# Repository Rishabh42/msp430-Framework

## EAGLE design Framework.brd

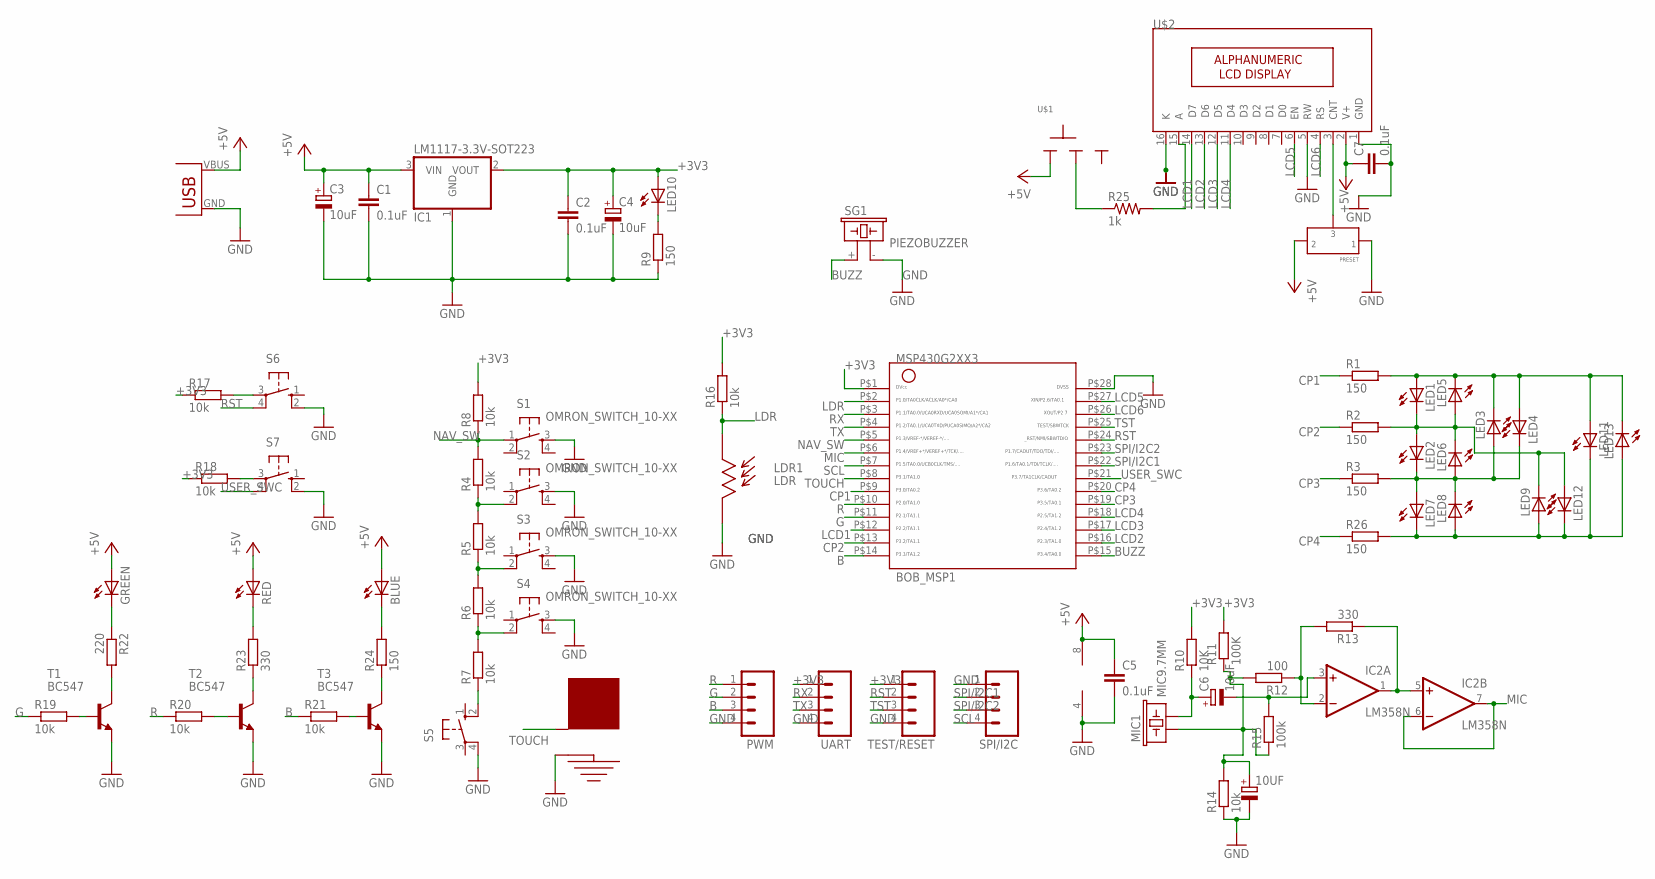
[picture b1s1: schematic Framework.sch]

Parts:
10UF: CAPACITOR-ELECTROLYTICE2.5-6; E2,5-6
BLUE: LED-BLU-5MM; LED-5MM
BOB_MSP1: BOB_MSP_28PIN
C1, C2, C5, C7: 0.1uF; C025-025X050
C3, C4, C6: 10uF; E2,5-6
GREEN: LED-RED-5MM; LED-5MM
IC1: LM1117-3.3V-SOT223; SOT223
IC2: LM358N; DIL08
LDR1: LDR; LDR-5MM
LED1, LED2, LED3, LED4, LED5, LED6, LED7, LED8, LED9, LED10, LED11, LED12, LED13: LED-RED-3MM; LED-3MM
MIC1: MIC9.7MM; MIC-9.7MM
PWM: M04; 04P
R1, R2, R3, R9, R24, R26: 150; 0204/7
R4, R5, R6, R7, R8, R14, R16, R17, R18, R19, R20, R21: 10k; 0204/7
R10: 10K; 0204/7
R11: 100K; 0204/7
R12: 100; 0204/7
R13, R23: 330; 0204/7
R15: 100k; 0204/7
R22: 220; 0204/7
R25: 1k; 0207/10
RED: LED-GRN-5MM; LED-5MM
S1, S2, S3, S4: OMRON_SWITCH_10-XX; B3F-10XX
S5: PUSH-BUTTON-6MM; B3F-10XX
S6, S7: 10-XX; B3F-10XX
SG1: PIEZOBUZZER
SPI/I2C: M04; 04P
T1, T2, T3: BC547; TO92
TEST/RESET: M04; 04P
TOUCH1: TOUCHPAD-20MM
U$1: SLIDE-SWITCH-BIG; SLIDE-SPDT-2.5X5-WITH-SUPPORT
U$2: CHAR-LCD-16X2; 16X2-LCD-WITH-MOUNT
U$3: USB-POWER; MINI-USB-POWER
U$4: PRESET; PRESET-LR
UART: M04; 04P

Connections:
+3V3: BOB_MSP1.P$1 (1), C2.1, C4.+, IC1.2 (VOUT), LED10.A, R8.2, R10.2, R11.2, R16.2, R17.1, R18.1, TEST/RESET.1, UART.1
B: BOB_MSP1.P$14 (14), PWM.3, R21.1
BLUE: BLUE.K (C), R24.2
BUZZ: BOB_MSP1.P$15 (15), SG1.+ (1)
CP1: BOB_MSP1.P$9 (9), R1.1
CP2: BOB_MSP1.P$13 (13), R2.1
CP3: BOB_MSP1.P$19 (19), R3.1
CP4: BOB_MSP1.P$20 (20), R26.1
G: BOB_MSP1.P$11 (11), PWM.2, R19.1
GND: 10UF.-, BOB_MSP1.P$28 (28), C1.2, C2.2, C3.-, C4.-, C5.2, C7.2, IC1.1 (GND), IC2.4 (V-), LDR1.P$2, PWM.4, R9.1, R14.1, S1.3 (S), S2.3 (S), S3.3 (S), S4.3 (S), S5.4 (P1), S6.2 (S1), S7.2 (S1), SG1.- (2), SPI/I2C.1, T1.1 (E), T2.1 (E), T3.1 (E), TEST/RESET.4, TOUCH1.GND, U$2.1 (GND), U$2.5 (RW), U$2.16 (K), U$3.GND, U$4.P$1 (1), UART.4
LCD1: BOB_MSP1.P$12 (12), U$2.14 (D7)
LCD2: BOB_MSP1.P$16 (16), U$2.13 (D6)
LCD3: BOB_MSP1.P$17 (17), U$2.12 (D5)
LCD4: BOB_MSP1.P$18 (18), U$2.11 (D4)
LCD5: BOB_MSP1.P$27 (27), U$2.6 (EN)
LCD6: BOB_MSP1.P$26 (26), U$2.4 (RS)
LDR: BOB_MSP1.P$2 (2), LDR1.P$1, R16.1
MIC: BOB_MSP1.P$6 (6), IC2.6 (-IN), IC2.7 (OUT)
unnamed: LED1.A, LED3.K (C), LED4.A, LED5.K (C), LED11.A, LED13.K (C), R1.2
unnamed: LED1.K (C), LED2.A, LED5.A, LED6.K (C), LED9.K (C), LED12.A, R2.2
unnamed: LED2.K (C), LED3.A, LED4.K (C), LED6.A, LED7.A, LED8.K (C), R3.2
unnamed: R4.1, R5.2, S2.2 (P1)
unnamed: R18.2, S7.3
unnamed: R5.1, R6.2, S3.2 (P1)
unnamed: R6.1, R7.2, S4.2 (P1)
unnamed: R7.1, S5.2 (S1)
unnamed: C6.+, MIC1.2, R10.1
unnamed: LED10.K (C), R9.2
unnamed: C6.-, IC2.3 (+IN), R15.2
unnamed: 10UF.+, MIC1.1, R11.1, R12.2, R14.2, R15.1
unnamed: R24.1, T3.3 (C)
unnamed: IC2.2 (-IN), R12.1, R13.2
unnamed: IC2.1 (OUT), IC2.5 (+IN), R13.1
unnamed: LED7.K (C), LED8.A, LED9.A, LED11.K (C), LED12.K (C), LED13.A, R26.2
unnamed: R17.2, S6.3
unnamed: R25.2, U$2.15 (A)
unnamed: R19.2, T1.2 (B)
unnamed: R22.2, T1.3 (C)
unnamed: GREEN.K (C), R22.1
unnamed: R25.1, U$1.2
unnamed: R23.2, RED.K (C)
unnamed: R23.1, T2.3 (C)
unnamed: R20.2, T2.2 (B)
unnamed: R21.2, T3.2 (B)
unnamed: U$2.3 (CNT), U$4.P$3 (3)
NAV_SW: BOB_MSP1.P$5 (5), R4.2, R8.1, S1.1
R: BOB_MSP1.P$10 (10), PWM.1, R20.1
RST: BOB_MSP1.P$24 (24), S6.4 (P1), TEST/RESET.2
RX: BOB_MSP1.P$3 (3), UART.2
SCL: BOB_MSP1.P$7 (7), SPI/I2C.4
SPI/I2C1: BOB_MSP1.P$22 (22), SPI/I2C.2
SPI/I2C2: BOB_MSP1.P$23 (23), SPI/I2C.3
TOUCH: BOB_MSP1.P$8 (8), TOUCH1.TOUCH
TST: BOB_MSP1.P$25 (25), TEST/RESET.3
TX: BOB_MSP1.P$4 (4), UART.3
USER_SWC: BOB_MSP1.P$21 (21), S7.4 (P1)
VCC: BLUE.A, C1.1, C3.+, C5.1, C7.1, GREEN.A, IC1.3 (VIN), IC2.8 (V+), RED.A, U$1.1, U$2.2 (V+), U$3.VBUS (VCC), U$4.P$2 (2)

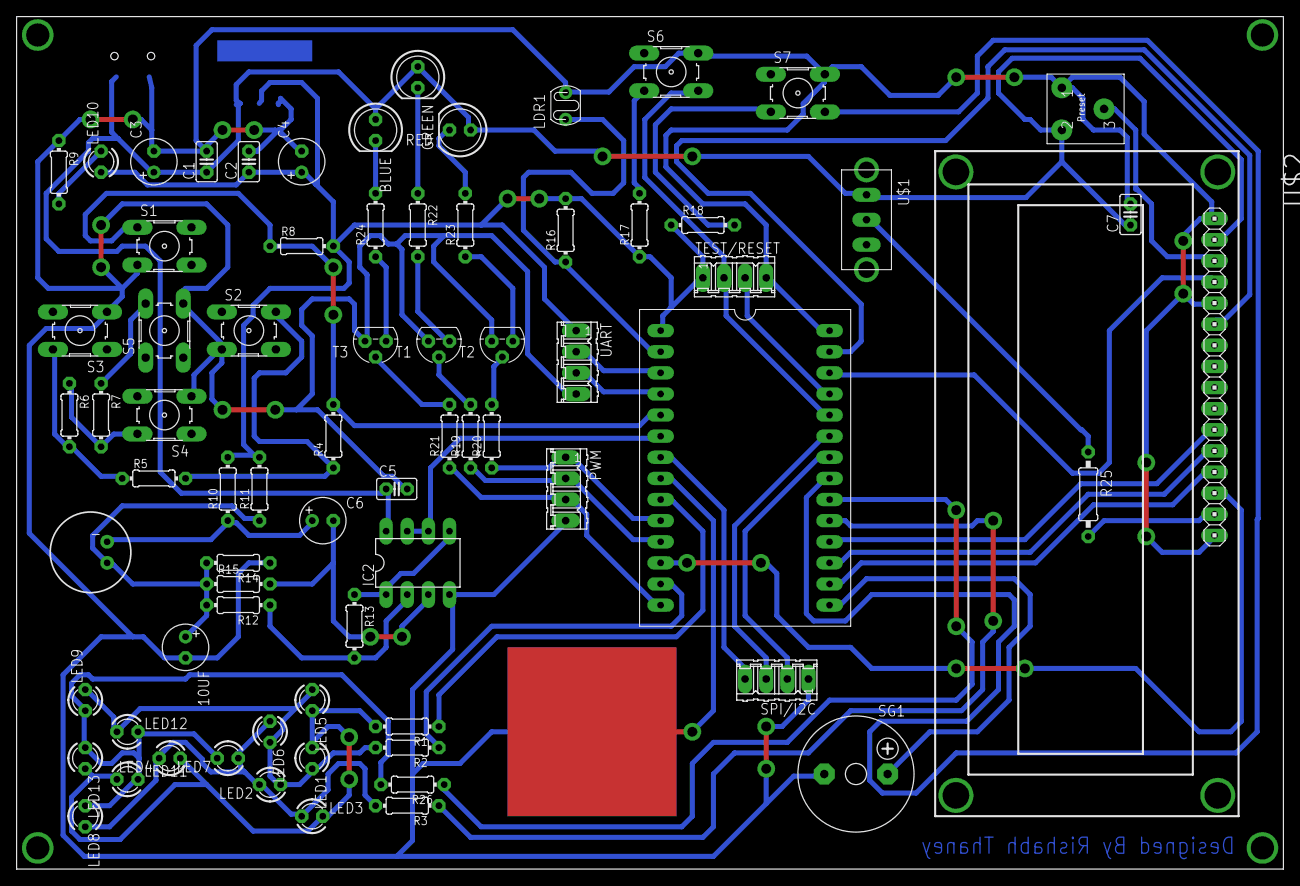
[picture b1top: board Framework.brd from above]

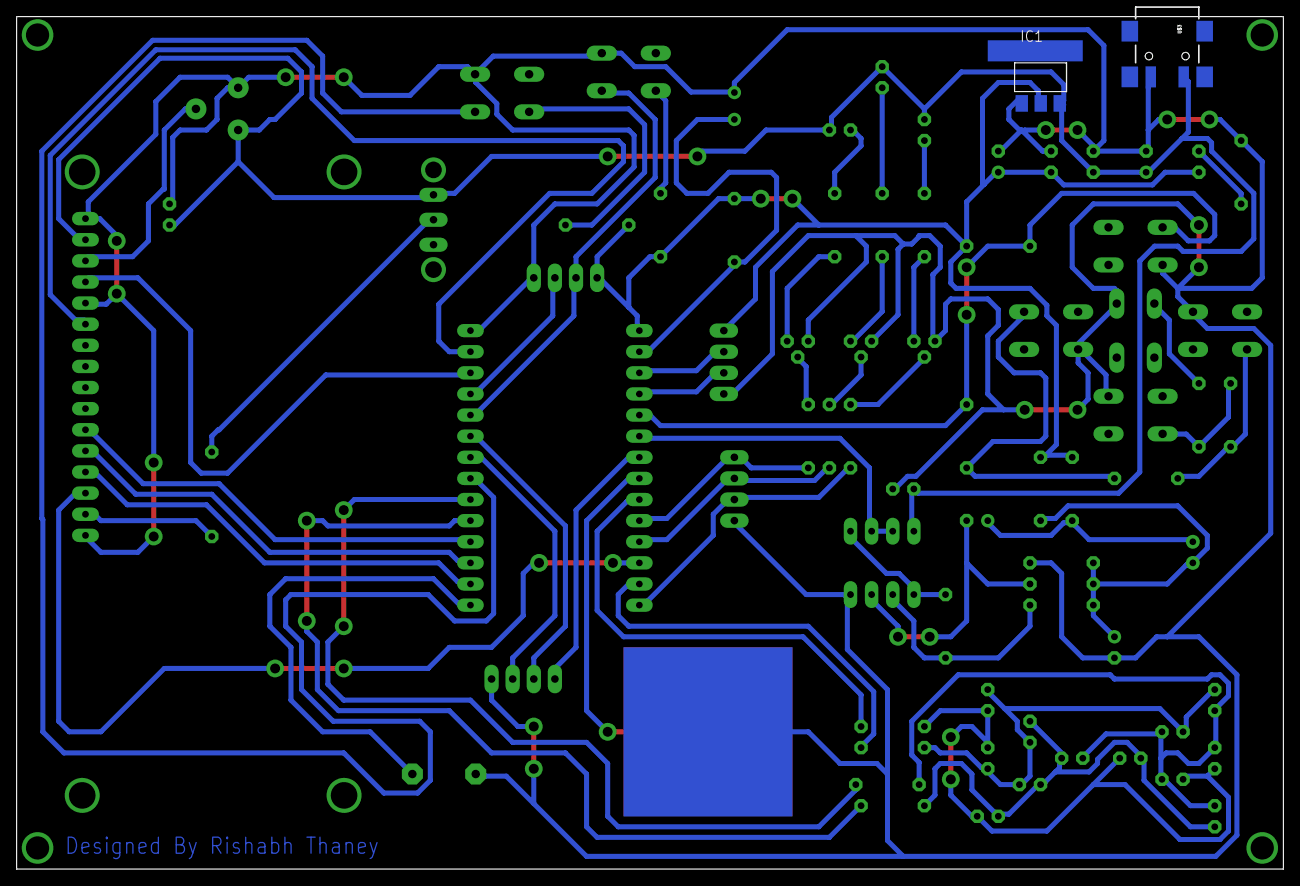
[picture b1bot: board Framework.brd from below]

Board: 2 copper layers, 152.4 x 102.5 mm, 75 parts (2 on the bottom side), 57 nets.
